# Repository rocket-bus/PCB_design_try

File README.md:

# PCB_design_try
 PCB_design_try

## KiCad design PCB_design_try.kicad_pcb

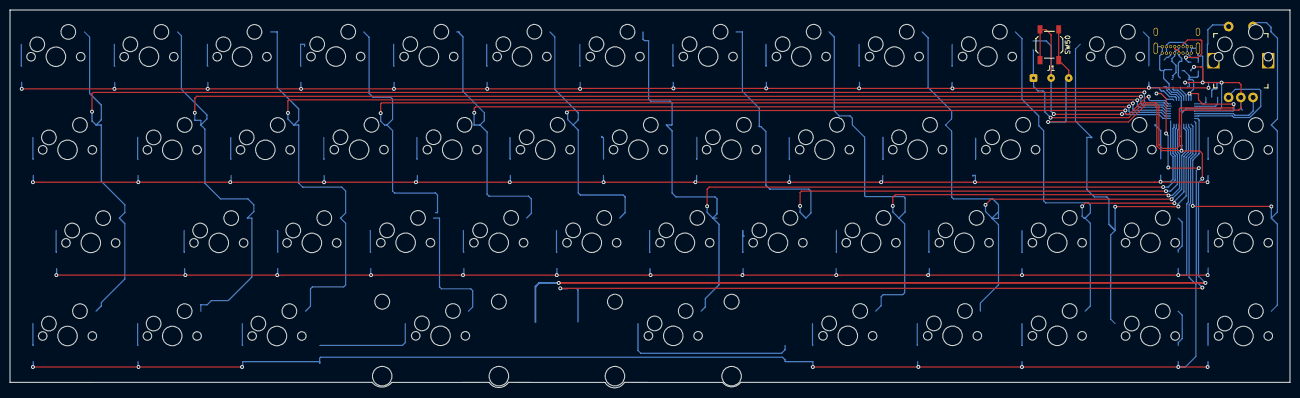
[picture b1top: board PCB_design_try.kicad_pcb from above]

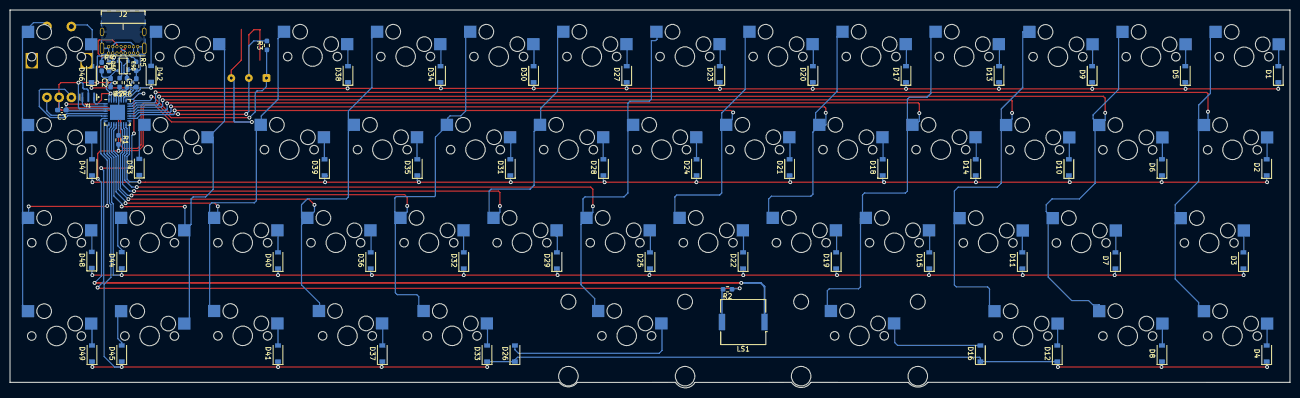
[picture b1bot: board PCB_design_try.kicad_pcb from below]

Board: 2 copper layers, 261.9 x 77.3 mm, 117 parts (65 on the bottom side), 84 nets.

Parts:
C1: 1uF; C_0603_1608Metric_Pad1.08x0.95mm_HandSolder
C2: 10uF; C_0603_1608Metric_Pad1.08x0.95mm_HandSolder
C3: 0.1uF; C_0603_1608Metric_Pad1.08x0.95mm_HandSolder
D1, D2, D3, D4, D5, D6, D7, D8, D9, D10, D11, D12, D13, D14, D15, D16, D17, D18, D19, D20, D21, D22, D23, D24, D25, D26, D27, D28, D29, D30, D31, D32, D33, D34, D35, D36, D37, D38, D39, D40, D41, D42, D43, D44, D45, D46, D47, D48, D49: D_Small; D_SOD-123
D50: PRTR5V0U2X; SOT-143B
F1: 500mA; Fuse_0603_1608Metric_Pad1.05x0.95mm_HandSolder
J1: Conn_01x03; SolderWire-0.1sqmm_1x03_P3.6mm_D0.4mm_OD1mm
J2: USB_C_Receptacle_USB2.0; USB_C_GCT_USB4085
LS1: Speaker; Buzzer_Murata_PKMCS0909E
R1, R3: 10k; R_0603_1608Metric_Pad0.98x0.95mm_HandSolder
R2: 1k; R_0603_1608Metric_Pad0.98x0.95mm_HandSolder
R4, R5: 5.1k; R_0603_1608Metric_Pad0.98x0.95mm_HandSolder
R6, R7: 22k; R_0603_1608Metric_Pad0.98x0.95mm_HandSolder
SW1, SW5, SW6, SW7, SW8, SW9, SW10, SW11, SW13, SW14, SW15, SW17, SW18, SW19, SW20, SW21, SW22, SW23, SW24, SW25, SW27, SW28, SW29, SW30, SW31, SW32, SW33, SW34, SW35, SW36, SW38, SW39, SW40, SW41, SW44, SW45, SW46, SW47, SW48, SW49: SW_Push; MXOnly-1U-Hotswap
SW2, SW4, SW12, SW37: SW_Push; MXOnly-1.25U-Hotswap
SW3, SW42: SW_Push; MXOnly-1.75U-Hotswap
SW16: SW_Push; MXOnly-2.25U-Hotswap
SW26: SW_Push; MXOnly-2.75U-Hotswap
SW43: SW_Push; MXOnly-1.5U-Hotswap
SW50: SW_Push; SW_SPST_TL3342
SW51: RotaryEncoder_Switch; RotaryEncoder_EC12E
U1: ATmega32U2-M; QFN-32-1EP_5x5mm_P0.5mm_EP3.1x3.1mm
Y1: CSTCE16M0V53-R0; OSC_CSTCE16M0V53-R0

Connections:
+5V: C2.1, C3.1, D50.4 (VCC), F1.2, J1.1, R3.1, U1.4 (VCC), U1.31 (UVCC), U1.32 (AVCC)
Audio: R2.1, U1.25 (PC5)
D+: R6.2, U1.29 (D+)
D-: R7.2, U1.30 (D-)
GND: C1.2, C2.2, C3.2, D50.1 (GND), J1.3, J2.A1 (GND), J2.A12 (GND), J2.B1 (GND), J2.B12 (GND), J2.S1 (SHIELD), LS1.1, R1.2, R4.2, R5.2, SW50.1, SW51.C, U1.3 (GND), U1.28 (UGND), U1.33 (GND), Y1.2
unnamed: C1.1, U1.27 (UCAP)
unnamed: D1.2 (A), SW1.1
unnamed: D2.2 (A), SW2.1
unnamed: D3.2 (A), SW3.1
unnamed: D4.2 (A), SW4.1
unnamed: D5.2 (A), SW5.1
unnamed: D6.2 (A), SW6.1
unnamed: D7.2 (A), SW7.1
unnamed: D8.2 (A), SW8.1
unnamed: D9.2 (A), SW9.1
unnamed: D10.2 (A), SW10.1
unnamed: D11.2 (A), SW11.1
unnamed: D12.2 (A), SW12.1
unnamed: D13.2 (A), SW13.1
unnamed: D14.2 (A), SW14.1
unnamed: D15.2 (A), SW15.1
unnamed: D16.2 (A), SW16.1
unnamed: D17.2 (A), SW17.1
unnamed: D18.2 (A), SW18.1
unnamed: D19.2 (A), SW19.1
unnamed: D20.2 (A), SW20.1
unnamed: D21.2 (A), SW21.1
unnamed: D22.2 (A), SW22.1
unnamed: D23.2 (A), SW23.1
unnamed: D24.2 (A), SW24.1
unnamed: D25.2 (A), SW25.1
unnamed: D26.2 (A), SW26.1
unnamed: D27.2 (A), SW27.1
unnamed: D28.2 (A), SW28.1
unnamed: D29.2 (A), SW29.1
unnamed: D30.2 (A), SW30.1
unnamed: D31.2 (A), SW31.1
unnamed: D32.2 (A), SW32.1
unnamed: D33.2 (A), SW33.1
unnamed: D34.2 (A), SW34.1
unnamed: D35.2 (A), SW35.1
unnamed: D36.2 (A), SW36.1
unnamed: D37.2 (A), SW37.1
unnamed: D38.2 (A), SW38.1
unnamed: D39.2 (A), SW39.1
unnamed: D40.2 (A), SW40.1
unnamed: D41.2 (A), SW41.1
unnamed: D42.2 (A), SW42.2
unnamed: D43.2 (A), SW43.2
unnamed: D44.2 (A), SW44.2
unnamed: D45.2 (A), SW45.2
unnamed: D47.2 (A), SW47.1
unnamed: D48.2 (A), SW48.1
unnamed: D49.2 (A), SW49.1
unnamed: D50.2 (I/O1), J2.A6 (D+), J2.B6 (D+), R6.1
unnamed: D50.3 (I/O2), J2.A7 (D-), J2.B7 (D-), R7.1
unnamed: J2.A5 (CC1), R5.1
unnamed: J2.B5 (CC2), R4.1
unnamed: LS1.2, R2.2
unnamed: R1.1, U1.13 (~HWB/PD7)
unnamed: U1.1 (XTAL1), Y1.1
unnamed: U1.2 (PC0/XTAL2), Y1.3
RESET: J1.2, R3.2, SW50.2, U1.24 (PC1/~RESET)
RE_1: D46.2 (A), SW46.1, SW51.S2
RE_2: SW46.2, SW47.2, SW48.2, SW49.2, SW51.S1, U1.7 (PD1)
RE_A: SW51.B, U1.5 (PC2)
RE_B: SW51.A, U1.6 (PD0)
VCC: F1.1, J2.A4 (VBUS), J2.A9 (VBUS), J2.B4 (VBUS), J2.B9 (VBUS)
col0: SW1.2, SW2.2, SW3.2, SW4.2, U1.23 (PC6)
col1: SW5.2, SW6.2, SW7.2, SW8.2, U1.22 (PC7)
col2: SW9.2, SW10.2, SW11.2, SW12.2, U1.21 (PB7)
col3: SW13.2, SW14.2, SW15.2, SW16.2, U1.20 (PB6)
col4: SW17.2, SW18.2, SW19.2, U1.19 (PB5)
col5: SW20.2, SW21.2, SW22.2, U1.18 (PB4)
col6: SW23.2, SW24.2, SW25.2, SW26.2, U1.16 (PB2)
col7: SW27.2, SW28.2, SW29.2, U1.15 (PB1)
col8: SW30.2, SW31.2, SW32.2, SW33.2, U1.14 (PB0)
col9: SW34.2, SW35.2, SW36.2, SW37.2, U1.12 (PD6)
col10: SW38.2, SW39.2, SW40.2, SW41.2, U1.11 (PD5)
col11: SW42.1, SW43.1, SW44.1, SW45.1, U1.10 (PD4)
row0: D1.1 (K), D5.1 (K), D9.1 (K), D13.1 (K), D17.1 (K), D20.1 (K), D23.1 (K), D27.1 (K), D30.1 (K), D34.1 (K), D38.1 (K), D42.1 (K), D46.1 (K), U1.26 (PC4)
row1: D2.1 (K), D6.1 (K), D10.1 (K), D14.1 (K), D18.1 (K), D21.1 (K), D24.1 (K), D28.1 (K), D31.1 (K), D35.1 (K), D39.1 (K), D43.1 (K), D47.1 (K), U1.17 (PB3)
row2: D3.1 (K), D7.1 (K), D11.1 (K), D15.1 (K), D19.1 (K), D22.1 (K), D25.1 (K), D29.1 (K), D32.1 (K), D36.1 (K), D40.1 (K), D44.1 (K), D48.1 (K), U1.9 (PD3)
row3: D4.1 (K), D8.1 (K), D12.1 (K), D16.1 (K), D26.1 (K), D33.1 (K), D37.1 (K), D41.1 (K), D45.1 (K), D49.1 (K), U1.8 (PD2)

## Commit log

2022-01-28 Add submodules
2022-01-28 Added footprint library
2022-01-28 MCU finished
2022-02-01 test
2022-02-01 scm_finished
2022-02-01 Kairo-kannsei
2022-02-04 2022/02/03 Update
2022-02-04 check
2022-02-08 pcb finished
2022-02-10 fixed
2022-02-14 Save
